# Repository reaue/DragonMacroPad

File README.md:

# DragonMacroPad

A macro pad with 8 switches, one rotary encoder, one OLED display and of course some RGB. It uses [QMK](https://qmk.fm/) firmware.

# CAD model

The full case and the pcb are connected by four M3x13mm screws and M3x5mx4mm heatset inserts, the inserts come under the `Top_case` and your screw the all macro pad by the bottom of the `Bottom_case`, like a sandwich with the pcb in the middle.

# Case parts

### Top_case

### Bottom_case

# PCB

### Schematic

### PCB

### The 3D model

# Firmware

I use QMK for this DragonMacroPad.

Here, keys binding (in order, starting from the top right) :
- RGB Toggle
- RGB Mode Switch
- Previous Track
- Next Track
- Copy
- Paste
- Undo
- Redo

- The rotary encoder changes Volume and if it's press switch between Play/Pause.

# BOM

The real one is in the repo.

| Component | Quantity |
|---|---:|
| XIAO RP2040 | 1 |
| Cherry MX Switches | 8 |
| EC11 Rotary Encoder | 1 |
| WS2812 RGB LED | 8 |
| 0.91" 128x32 OLED Display | 1 |
| 1N4148 DO-35 Diodes | 9 |
| DSA Keycaps | 8 |
| PCB | 1 |
| M3x13mm | 4 |
| M3 M3x5x4 Heatset inserts | 4 |
| Case (2 printed parts )| 1 |
| EC11 Knob ( printed part )| 1 |

# Possible improvement

Take switches which are Led SMD compatible (such as Gateron SMD Yellow), because Cherry MX Switches do not let pass so much light.

# Credits

I used [QMK](https://qmk.fm/) and [Kicad](https://www.kicad.org/).
Moreover, I used one 3D model from [Ziemniaczenka](https://www.printables.com/@Ziemniaczenka)

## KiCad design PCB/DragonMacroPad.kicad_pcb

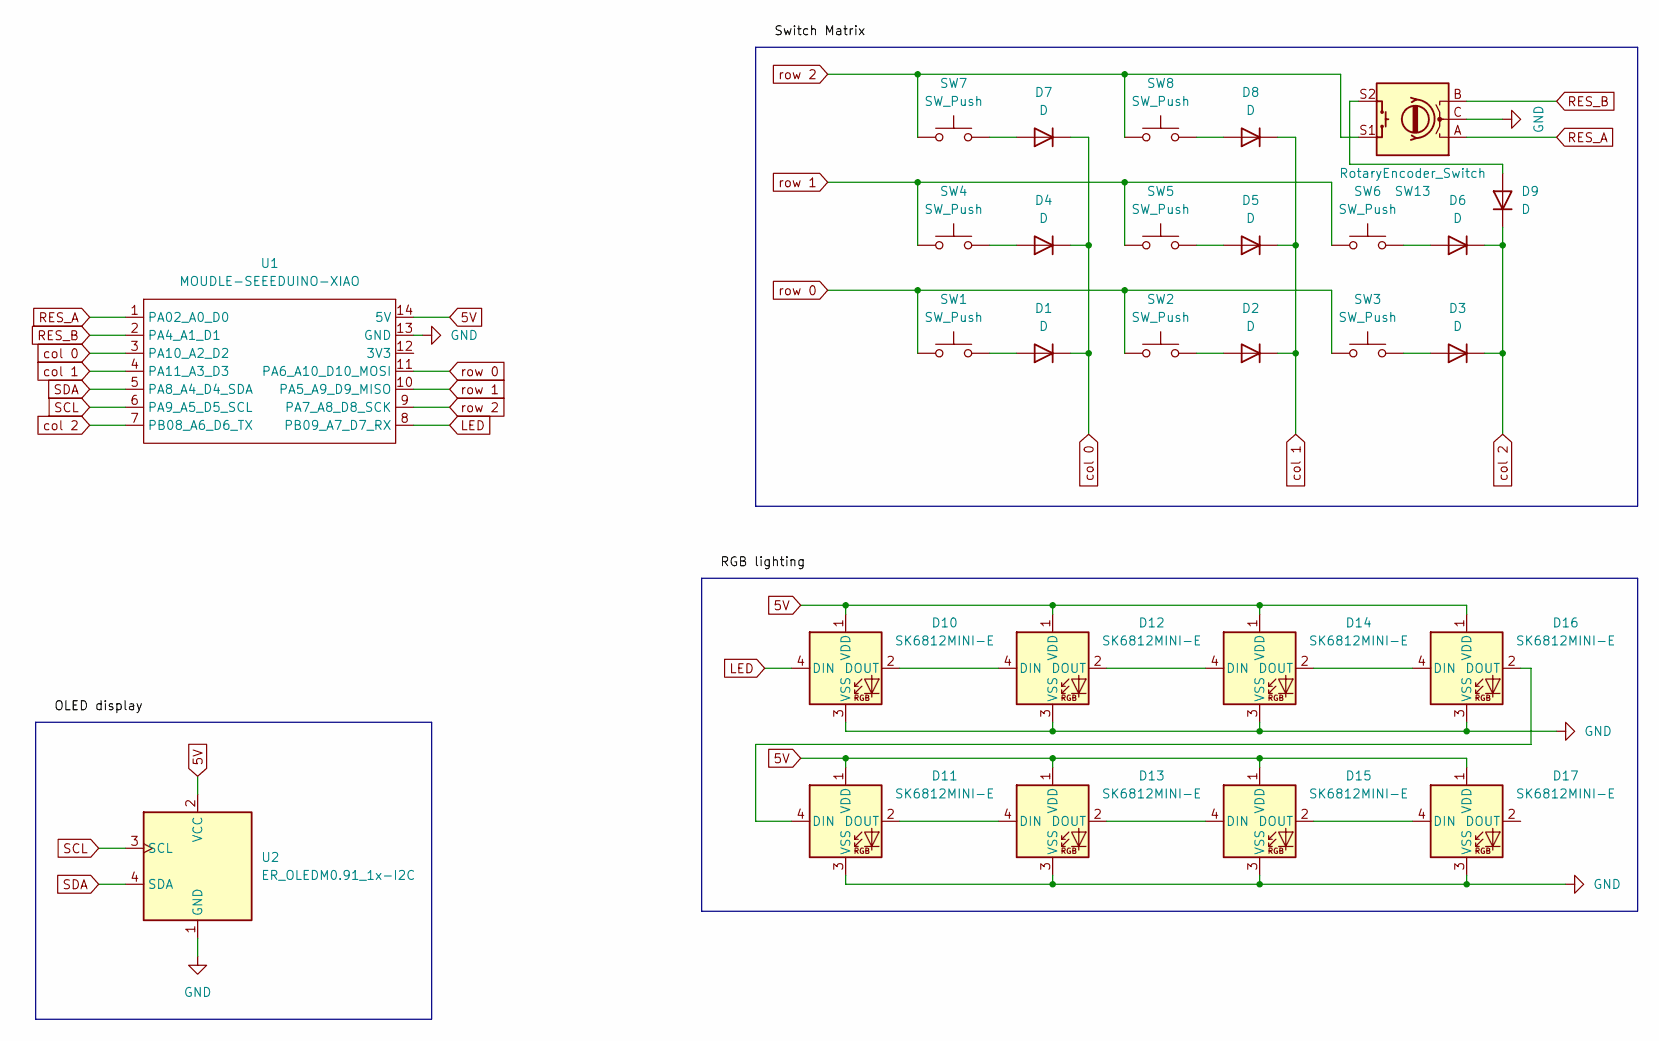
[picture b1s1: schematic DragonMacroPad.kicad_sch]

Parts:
D1, D2, D3, D4, D5, D6, D7, D8, D9: D; D_DO-35_SOD27_P7.62mm_Horizontal
D10, D11, D12, D13, D14, D15, D16, D17: SK6812MINI-E; SK6812MINI-E_fixed
SW1, SW2, SW3, SW4, SW5, SW6, SW7, SW8: SW_Push; SW_Cherry_MX_1.00u_PCB
SW13: RotaryEncoder_Switch; RotaryEncoder_Alps_EC11E-Switch_Vertical_H20mm
U1: MOUDLE-SEEEDUINO-XIAO; XIAO-Generic-Hybrid-14P-2.54-21X17.8MM
U2: ER_OLEDM0.91_1x-I2C; SSD1306-0.91-OLED-4pin-128x32

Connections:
5V: D10.1 (VDD), D11.1 (VDD), D12.1 (VDD), D13.1 (VDD), D14.1 (VDD), D15.1 (VDD), D16.1 (VDD), D17.1 (VDD), U1.14 (5V), U2.2 (VCC)
GND: D10.3 (VSS), D11.3 (VSS), D12.3 (VSS), D13.3 (VSS), D14.3 (VSS), D15.3 (VSS), D16.3 (VSS), D17.3 (VSS), SW13.C, U1.13 (GND), U2.1 (GND)
LED: D10.4 (DIN), U1.8 (PB09_A7_D7_RX)
unnamed: D1.2 (A), SW1.2
unnamed: D2.2 (A), SW2.2
unnamed: D3.2 (A), SW3.2
unnamed: D4.2 (A), SW4.2
unnamed: D5.2 (A), SW5.2
unnamed: D6.2 (A), SW6.2
unnamed: D7.2 (A), SW7.2
unnamed: D8.2 (A), SW8.2
unnamed: D9.2 (A), SW13.S2
unnamed: D10.2 (DOUT), D12.4 (DIN)
unnamed: D11.4 (DIN), D16.2 (DOUT)
unnamed: D11.2 (DOUT), D13.4 (DIN)
unnamed: D12.2 (DOUT), D14.4 (DIN)
unnamed: D13.2 (DOUT), D15.4 (DIN)
unnamed: D14.2 (DOUT), D16.4 (DIN)
unnamed: D15.2 (DOUT), D17.4 (DIN)
RES_A: SW13.A, U1.1 (PA02_A0_D0)
RES_B: SW13.B, U1.2 (PA4_A1_D1)
SCL: U1.6 (PA9_A5_D5_SCL), U2.3 (SCL)
SDA: U1.5 (PA8_A4_D4_SDA), U2.4 (SDA)
col 0: D1.1 (K), D4.1 (K), D7.1 (K), U1.3 (PA10_A2_D2)
col 1: D2.1 (K), D5.1 (K), D8.1 (K), U1.4 (PA11_A3_D3)
col 2: D3.1 (K), D6.1 (K), D9.1 (K), U1.7 (PB08_A6_D6_TX)
row 0: SW1.1, SW2.1, SW3.1, U1.11 (PA6_A10_D10_MOSI)
row 1: SW4.1, SW5.1, SW6.1, U1.10 (PA5_A9_D9_MISO)
row 2: SW7.1, SW8.1, SW13.S1, U1.9 (PA7_A8_D8_SCK)

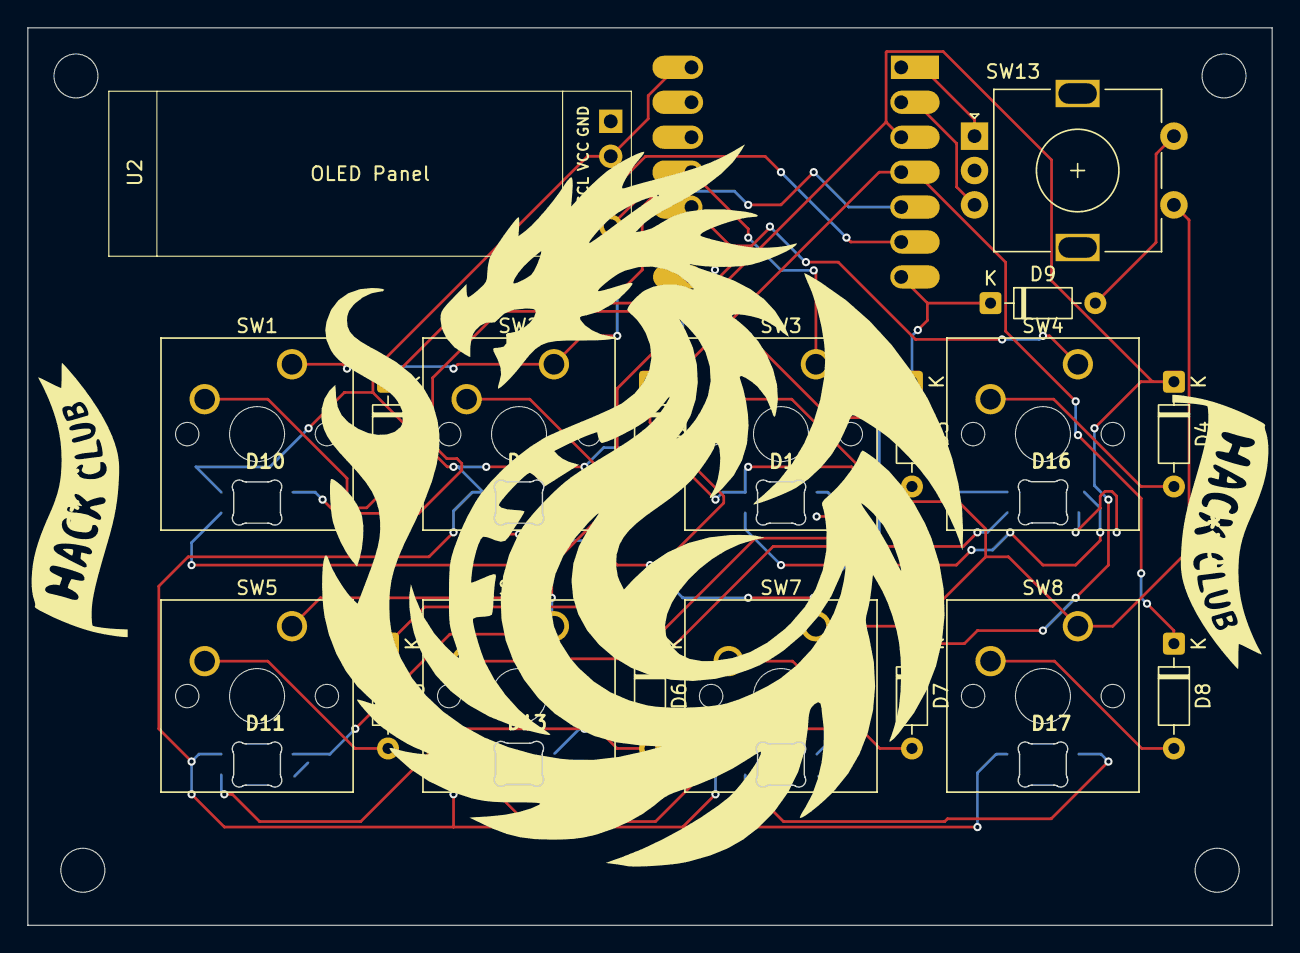
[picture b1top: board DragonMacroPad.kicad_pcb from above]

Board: 2 copper layers, 90.5 x 65.3 mm, 28 parts (1 on the bottom side), 29 nets.
